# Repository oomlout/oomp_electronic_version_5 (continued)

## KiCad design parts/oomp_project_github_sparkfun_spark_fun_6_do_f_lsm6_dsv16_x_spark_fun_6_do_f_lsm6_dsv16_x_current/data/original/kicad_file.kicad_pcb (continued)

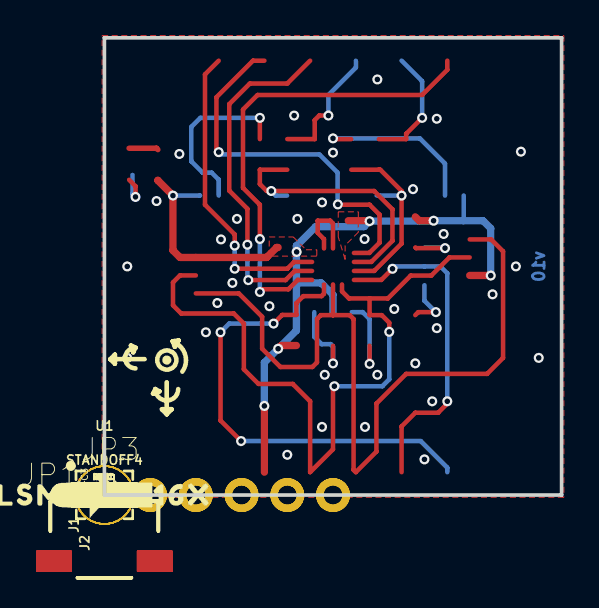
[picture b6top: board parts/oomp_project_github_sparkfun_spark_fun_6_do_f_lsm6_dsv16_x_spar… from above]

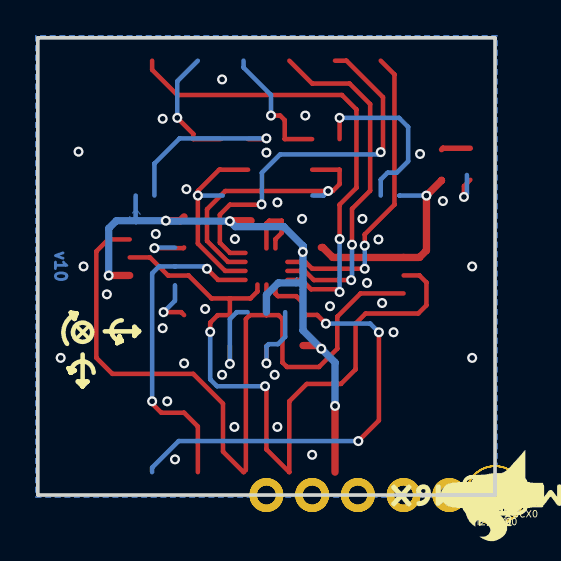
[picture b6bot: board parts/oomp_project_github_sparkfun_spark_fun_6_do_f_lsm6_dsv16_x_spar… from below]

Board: 2 copper layers, 25.4 x 25.4 mm, 87 parts (40 on the bottom side), 22 nets.

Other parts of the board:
U$1, U$15: #3V3#1
U$2, U$17: #GND#0
U$3: ##CS##7
U$4: #SDA#4
U$5: #SCL#5
U$6: #POCI#11
U$7: INT16
U$8: #INT2#2
U$9: OCS17
U$10: SCX18
U$11: SDX19
U$12: #AH1#32
U$13: #0X6A#11
U$14: #0X6B#11
U$16: #LED#4
U$18: #POCI#12
U$19: #AH2#32
U$20: #OCS#32
U$21: #INT1#25
U$23: #PAD1#4
U$24: #POCIX#8
U$25: #I2C#11
U$26: #PICO#13
U$27: ##CS##8
U$28: PWR8
U$29: SFE_LOGO_FLAME_.1
U$30: #PAD2#4
U$31: 6DOF12
U$32: #1#729
U$33: #POCIX#7
U$34, U$37: X2114
U$35, U$38: Y2115
U$36, U$39: Z2116
U$40: #INT2#3
U$41: #1#4
U$42: #SDX#20
U$43: #SCX#19
U$44: SFE_LOGO_FLAME_.2
U$45, U$49: #0#4
U$46, U$47: LSM6DSV16X37
U$48: #SCLK#4

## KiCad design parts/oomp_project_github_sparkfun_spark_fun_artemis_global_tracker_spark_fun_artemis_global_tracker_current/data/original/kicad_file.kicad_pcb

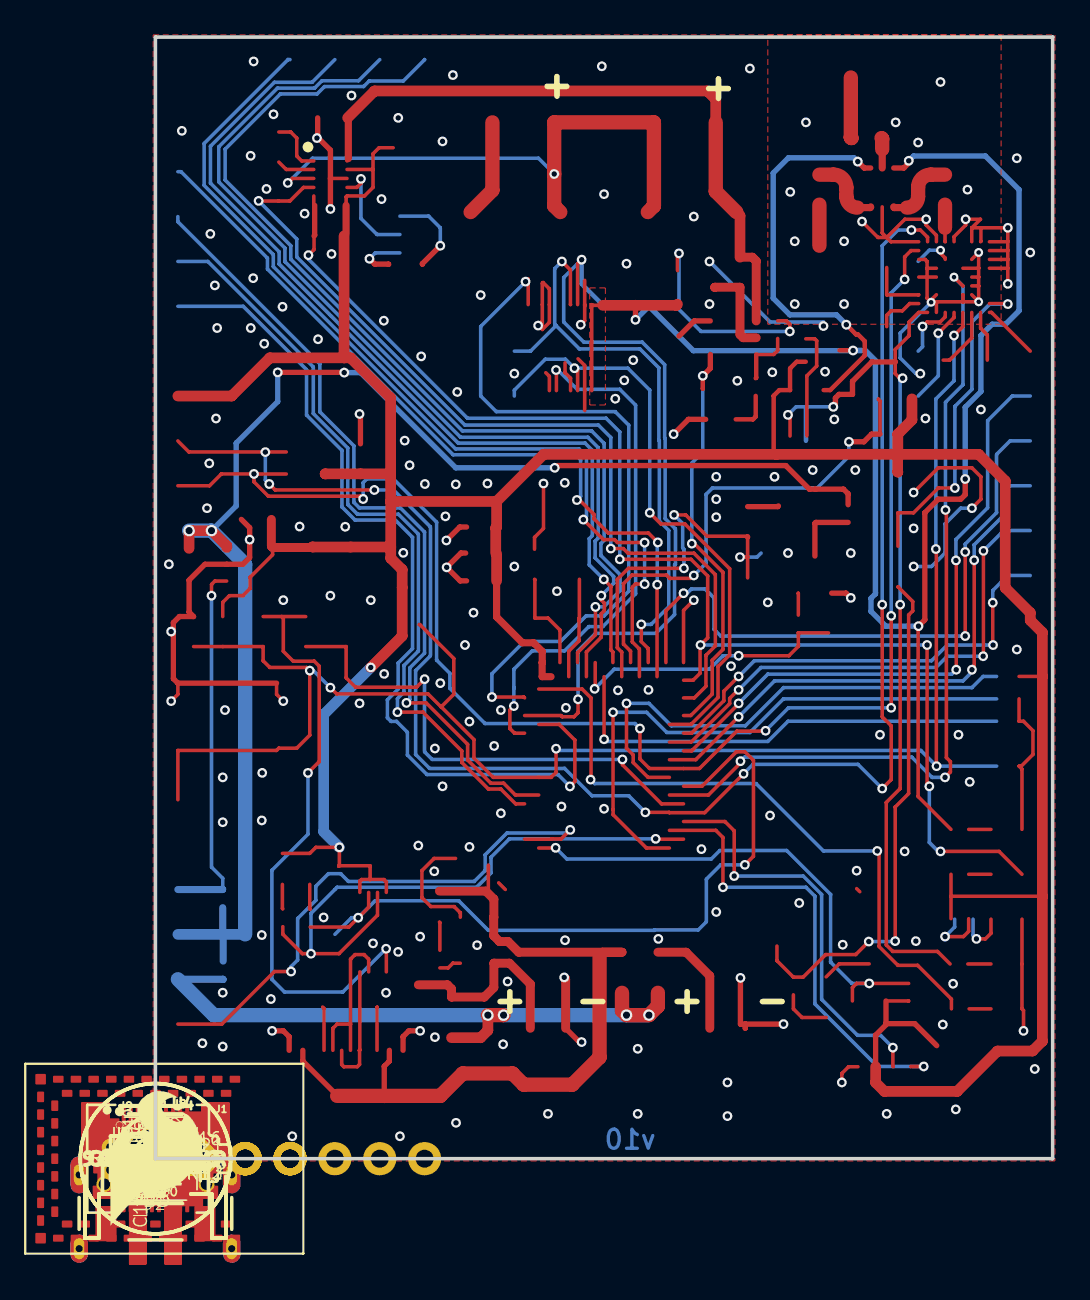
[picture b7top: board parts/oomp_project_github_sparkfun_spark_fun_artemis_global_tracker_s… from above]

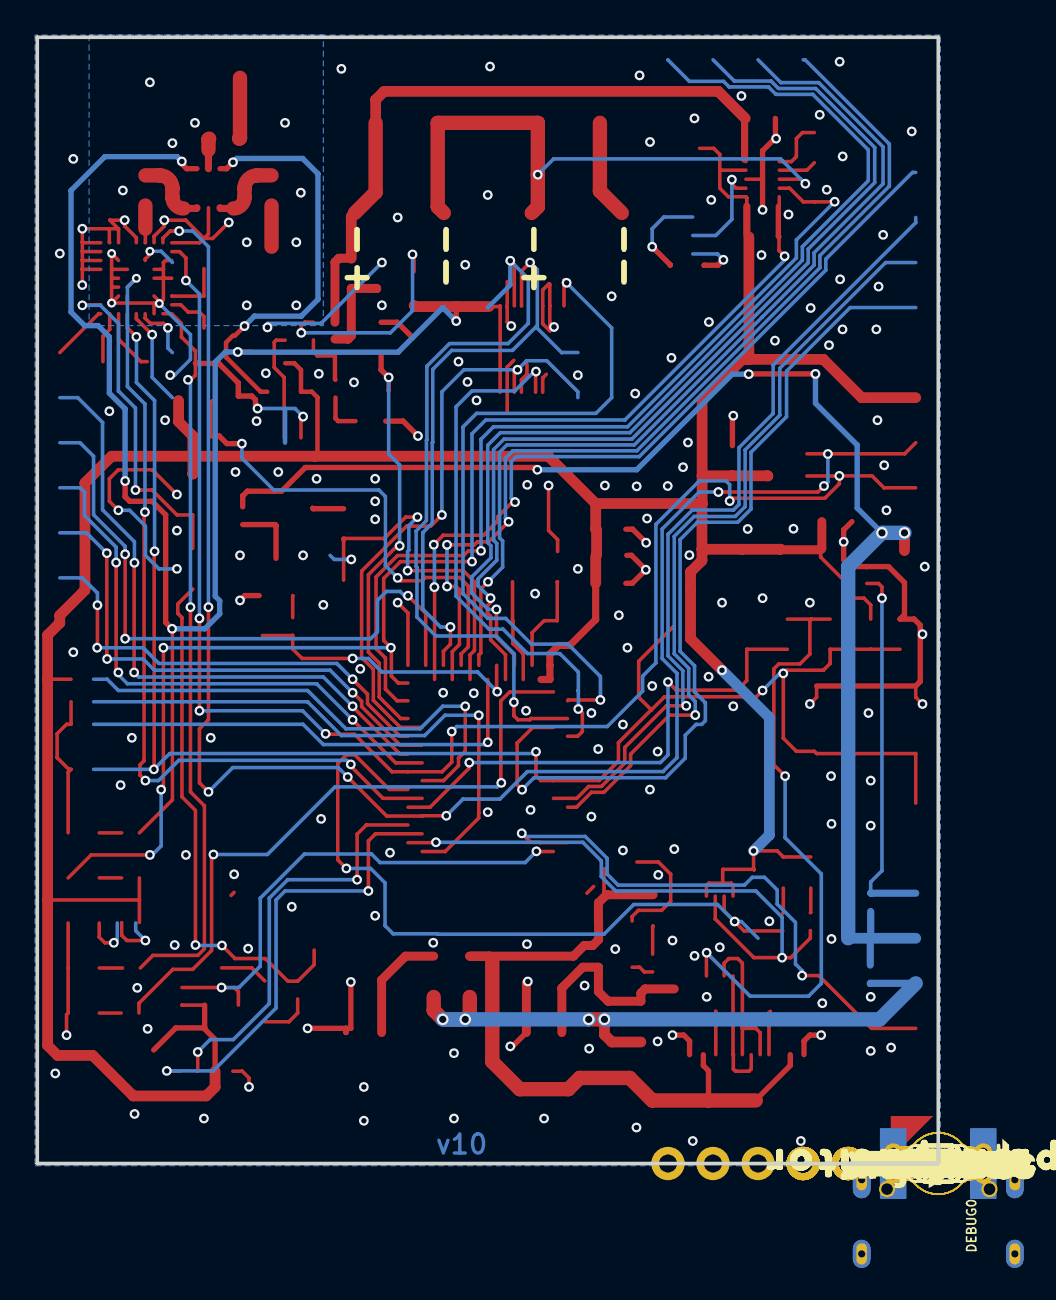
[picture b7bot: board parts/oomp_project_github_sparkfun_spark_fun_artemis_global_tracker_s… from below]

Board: 2 copper layers, 50.8 x 63.5 mm, 240 parts (79 on the bottom side), 101 nets.

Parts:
!RESET0: 1X01_NO_SILK
B1: ML414H_IV01E_BATTERY; ML414H_IV01E
C1, C9: 10nF; 0603
C2: 2.2uF; 0603
C3, C10, C23, C24, C27: 1.0uF; 0603
C4, C12: 0.22uF; 0603
C5, C6: 1F 2.7V; CPOL-RADIAL-1F-2.7V
C7, C13, C20, C28, C30, C31: 0.1uF; 0603
C8, C11, C17: 4.7uF; 0603
C14, C15, C16: 100pF; 0603
C18, C19: 15pF; 0603
C21, C25: 22uF; 0805
C22: 10uF; 0603
C29: 1nF; 0603
D1, D7: GREEN; LED-0603
D2, D9, D13: Yellow; LED-0603
D3: RED; LED-0603
D4: BLUE; LED-0603
D5, D8, D10, D11, D12, D14: 0.5A/40V/420mV; SOD-323
D6: WHITE; LED-0603
D17, D41: PAD.03X.05
DEBUG0: CORTEX_DEBUG; 2X5-PTH-1.27MM-NO_SILK
EN0: 1X01_NO_SILK
FRAME3: FRAME-LETTERNO_PACKAGE; DUMMY
FRAME5: FRAME-LEDGER; CREATIVE_COMMONS
GND0: 1X01_NO_SILK
GPS_RX0: TEST-POINT3X5; PAD.03X.05
GPS_TX0: TEST-POINT3X5; PAD.03X.05
I2C0: PTH; 1X04_NO_SILK
J1: IRIDIUM_9603N
J2: USB-C; USB-C-16P-2LAYER-PADS
J3, J5: JST-2-SMD
J4: 1X02_NO_SILK
J6: U.FL
J7: ANTENNA-GROUNDEDEDGE_SMA; SMA-EDGE
J8, J9: STAND-OFF-REFLOW-M2.0_6.0MM_TALL; STAND-OFF-REFLOW-M2.0
J10, J11: 1X04_NO_SILK
J13: 1X01_NO_SILK
JP1: JUMPER-SMT_3_1-NC_TRACE_SILK; SMT-JUMPER_3_1-NC_TRACE_SILK
JP2: JUMPER-SMT_2_NC_TRACE_SILK; SMT-JUMPER_2_NC_TRACE_SILK
JP7, JP8, JP13, JP14: FIDUCIAL1X2; FIDUCIAL-1X2
JP9, JP10, JP11, JP12: STAND-OFF
L1: 2.2uH; 0806
LOGO1: SFE_LOGO_NAME.1_INCH; SFE_LOGO_NAME_.1
LOGO2: SFE_LOGO_FLAME.3_INCH; SFE_LOGO_FLAME_.3
LOGO4: OSHW-LOGOMINI; OSHW-LOGO-MINI
MEAS0: JUMPER-SMT_2_NC_TRACE_SILK; SMT-JUMPER_2_NC_TRACE_SILK
Q1: 5.8A/30V/35mΩ; SOT23-3
Q2, Q3, Q6: 20V/4.2A/52mΩ/1.4W; SOT23-3
Q4: 600mA/40V; SOT23-3
QWIIC0: QWIIC_RA; JST04_1MM_RA
R1: 330; 0402-TIGHT
R2, R3, R12, R16, R21, R25, R29: 1k; 0402-TIGHT
R4, R20: 5.1k; 0402-TIGHT
R5, R14, R17, R19, R22, R23, R30: 10K; 0402-TIGHT
R6: 12k; 0603
R7: 30.1k; 0603
R8, R26: 100k; 0603
R9: 0.015ohm; 0603
R10, R11: 100; 0402-TIGHT
R13, R28: 2.0K; 0402-TIGHT
R15: 3.3K; 0402-TIGHT
R24: 20k; 0603
R27: 220k; 0603
R31: 20k; 0402-TIGHT
RX0, RX1: TEST-POINT3X5; PAD.03X.05
S1: RESET; TACTILE_SWITCH_SMD_5.2MM
SAFEBOOT0: TEST-POINT3X5; PAD.03X.05
SC1+0, SC1-0, SC2+0, SC2-0: 1X01_NO_SILK
SPI0: 1X07_NO_SILK
TX0, TX1: TEST-POINT3X5; PAD.03X.05
U1: CH340E_MSOP10; MSOP10
U2: LTC3225EDDB; DFN300X200-10L
U3: ADM4210_1TSOT6; TSOT6
U4: u-blox_ZOE_M8Q-0-10; UBLOX_ZOE_M8-0-10
U5: AS179-92LF; SOT65P220X100-6N
U6: MS8607-02BA01
U7: ARTEMIS_MODULESMD; ARTEMIS_FP
U8: V_SUPERVISOR_BD48K24G_2.4V; SOT23-3
U9: MCP73831; SOT23-5
U10: 3.3V; SOT23-5
U11: 74LVC1G04SE; SOT353
U12: 74LVC1G08W5-7; SOT23-5
U$1, U$13: SUPERCAPACITOR151
U$2: #SCK#199608
U$3, U$43: #3V3#0
U$4: #SDA#0
U$5: #USB#C#0
U$6: #SCL#0
U$7: #VIN#158
U$8: #3V3SW#0
U$9: CHARGING9604
U$10: #COPI#9694
U$11: QWIIC_4MM
U$12: LIPO5
U$14, U$15: 10F_2#7V152
U$16: RX06
U$17, U$70: #3V3#153
U$18: TX07
U$19: #AD35#199609
U$20, U$36: #GND#0
U$21: #SDA#153
U$22: #SCL#154
U$24: #AD31#7
U$25: QWIIC_5MM
U$26: #_RST##156
U$27: #EN#157
U$28: #VIN#3#0
U$29: #AD35#0
U$30: ARTEMIS0
U$31: SUPERCAPS6
U$32: #D17#0
U$33: #SAFEBOOT#0
U$34: #TX0#0
U$35: #TX1#0
U$37: #RX#0
U$38: #RX1#0
U$39: #TX#0
U$40: #5#3V#0
U$41: #D41#0
U$42: #RX0#0
U$44: #RESET#162
U$45: #SOLAR#165
U$46: #LIPO#164
U$47: #MEAS#0
U$48: #3V3_#0
U$50: #D4#36
U$51: GLOBAL0
U$52: TRACKER0
U$53: #LIPO#0
U$54: #_EN_#0
U$55: #SOLAR#0
U$56: #USB#C#161
U$57: #3_X_AA#0
U$58: #VBUS#159
U$59: #AD32#152
U$60: #SCK#9696
U$61: #PWR_LED#0
U$63: #D4#5
U$64: #CIPO#2
U$65: #3_X_AAA#0
U$66: #6V_MAX#0
U$67: CHARGE8
U$69: CURRENT9
U$71: #D42#32
U$72: #D37#152
U$73: #D43#43
U$74: #150#61
U$75: #COPI#5
U$76, U$77, U$78: #GND#152
U$79: #A32#44
U$80: #MA#45
U$81: #60#46
U$82: #D43#151
U$83: #D42#151
U$84: #AD31#151
U$85: #AD12#151
U$86: #D15#151
U$87: #AD11#151
U$88: #AD29#151
U$89: #CIPO#151
U$90: #D37#0
U$91: #GND#38
U$92: ##RST##39
U$93: 9603N_PWR40
U$94: POWER9605
U$95: GNSS9606
U$96: D199607
UNK3V3EN0: JUMPER-SMT_2_NC_TRACE_SILK; SMT-JUMPER_2_NC_TRACE_SILK
UNK3V3SW0: PAD.03X.05
UNK5V3: TEST-POINT3X5; PAD.03X.05
VIN/3: TEST-POINT3X5; PAD.03X.05
X1, X2: 32.768kHz; CRYSTAL-SMD-3.2X1.5MM

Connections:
3.3V: C1.1, C2.1, C7.1, C12.1, C20.2, C22.1, C23.1, C24.1, C25.1, C27.1, C28.1, D7.A, D11.A, D13.A, DEBUG0.1, I2C0.2, Q2.2, Q6.2, QWIIC0.2, R1.2, R8.2, R12.2, R17.2, R19.2, R26.2, SPI0.7, U1.7, U1.10, U2.6, U2.9, U6.1, U7.VDD@36, U7.VDD@37, U8.3, U10.5, U11.5, U12.5
3V3SW: C13.1, Q2.3, R16.2, U4.24, U4.25, U12.1, UNK3V3SW0.1
ANTENNA: C16.1, J7.SIG
ARTEMIS_AD11: J11.3, U7.~AD11
ARTEMIS_AD12: J11.1, U7.~AD12
ARTEMIS_AD29: J11.4, U7.~AD29
ARTEMIS_AD31: J10.1, U7.~AD31
ARTEMIS_AD32: J10.4, U7.~AD32
ARTEMIS_BOOT: C30.2, R27.2, U7.BOOT
ARTEMIS_D4: SPI0.6, U7.~D4
ARTEMIS_D5_SCK: SPI0.4, U7.~D5
ARTEMIS_D6_MISO: SPI0.3, U7.~D6
ARTEMIS_D7_MOSI: SPI0.2, U7.D7
ARTEMIS_D8_SCL: I2C0.4, U4.32, U6.8, U7.D8
ARTEMIS_D9_SDA: I2C0.3, U4.2, U6.7, U7.D9
ARTEMIS_D10: U4.50, U7.D10
ARTEMIS_D13: R23.1, R24.2, U7.~AD13, VIN/3.1
ARTEMIS_D15: J11.2, U7.D15
ARTEMIS_D17: D17.1, J1.5, U7.D17
ARTEMIS_D18: J1.19, U7.~D18
ARTEMIS_D19: R21.2, U7.~D19
ARTEMIS_D22: R14.1, U3.3, U7.~D22
ARTEMIS_D24: J1.6, TX1.1, U7.~D24
ARTEMIS_D25: J1.7, RX1.1, U7.~D25
ARTEMIS_D26: Q2.1, R17.1, U7.~D26
ARTEMIS_D27: R5.2, U2.4, U7.~D27
ARTEMIS_D28: D2.C, R8.1, U2.5, U7.~D28
ARTEMIS_D33: DEBUG0.6, U7.~AD33/SWO
ARTEMIS_D34: R25.1, R30.1, U7.AD34
ARTEMIS_D35: SPI0.5, U7.~AD35
ARTEMIS_D37: J13.1, U7.~D37
ARTEMIS_D39_SCL4: QWIIC0.4, U7.~D39
ARTEMIS_D40_SDA4: QWIIC0.3, U7.D40
ARTEMIS_D41: D41.1, J1.12, U7.D41
ARTEMIS_D42: J10.2, U7.~D42
ARTEMIS_D43: J10.3, U7.~D43
ARTEMIS_D44: Q6.1, R19.1, U7.~D44
ARTEMIS_RX0: R2.1, RX0.1, U1.8, U7.RXI-0
ARTEMIS_SWDCK: DEBUG0.4, U7.SWDCK
ARTEMIS_SWDIO: DEBUG0.2, U7.SWDIO
ARTEMIS_TX0: R3.1, TX0.1, U1.9, U7.TXO-0
ARTEMIS_~RESET: !RESET0.1, C29.1, C31.2, DEBUG0.10, R26.1, S1.3, S1.4, U4.20, U7.~RST, U8.2
ARTEMIS_~RTS: C30.1, C31.1, U1.4
CC3: J2.B5, R4.2
CC4: J2.A5, R20.2
D+2: J2.A6, J2.B6, U1.1
D-2: J2.A7, J2.B7, U1.2
EXT_PWR: J1.1, J1.2, Q1.2, R13.2, U5.4, U11.2, UNK5V3.1
GND: B1.-, C1.2, C2.2, C4.2, C6.-, C7.2, C8.2, C9.2, C10.2, C11.2, C12.2, C13.2, C17.2, C18.1, C19.1, C20.1, C21.2, C22.2, C23.2, C24.2, C25.2, C27.2, C28.2, C29.2, D1.C, D3.C, D4.C, D6.C, DEBUG0.3, DEBUG0.5, DEBUG0.9, GND0.1, I2C0.1, J1.3, J1.4, J1.8, J1.13, J1.14, J1.15, J1.18, J2.GND, J2.GND2, J3.1, J5.1, J6.1, J6.2, J7.GND@0, J7.GND@1, J7.GND@2, J7.GND@3, J8.1, J9.1, Q4.2, QWIIC0.1, R4.1, R5.1, R6.1, R7.2, R14.2, R20.1, R23.2, R27.1, R28.1, R30.2, R31.2, S1.1, S1.2, SC2-0.1, SPI0.1, U1.3, U2.8, U2.11, U3.2, U4.1, U4.3, U4.5, U4.7, U4.8, U4.9, U4.10, U4.11, U4.12, U4.17, U4.23, U4.29, U4.31, U4.37, U4.38, U4.39, U4.40, U4.41, U4.44, U4.46, U4.47, U4.49, U5.2, U6.3, U7.GND@1, U7.GND@22, U7.GND@38, U7.GND@39, U7.GND@47, U7.GND@59, U8.1, U9.2, U10.2, U11.3, U12.3
GNSS: C15.2, U4.4
IRIDIUM: C14.2, J6.FEED
LTC3225_VOUT: C4.1, C5.+, R9.2, SC1+0.1, U2.10, U3.6
unnamed: C5.-, C6.+, SC1-0.1, SC2+0.1, U2.3
unnamed: JP1.3, R6.2
unnamed: JP2.2, R1.1
unnamed: JP1.1, R7.1
unnamed: D2.A, R12.1
unnamed: D3.A, R13.1
unnamed: D5.A, Q6.3
unnamed: Q1.3, R9.1, U3.5
unnamed: C3.2, U2.2
unnamed: C3.1, U2.1
unnamed: JP1.2, U2.7
unnamed: Q1.1, R10.1
unnamed: R10.2, R11.1, U3.4
unnamed: C9.1, R11.2
unnamed: C10.1, U3.1
unnamed: L1.2, U4.26
unnamed: C11.1, L1.1, U4.27
unnamed: U4.18, X2.P$2
unnamed: U4.19, X2.P$1
unnamed: D5.C, R15.2
unnamed: D4.A, R16.1
unnamed: D13.C, R2.2
unnamed: D1.A, JP2.1
unnamed: D11.C, D12.C, U4.16
unnamed: SAFEBOOT0.1, U4.34
unnamed: GPS_RX0.1, U4.22
unnamed: GPS_TX0.1, U4.21
unnamed: C14.1, U5.1
unnamed: C15.1, U5.3
unnamed: C16.2, U5.5
unnamed: R31.1, U5.6, U12.4
unnamed: D7.C, R3.2
unnamed: U11.4, U12.2
unnamed: D6.A, R21.1
unnamed: EN0.1, U10.3, UNK3V3EN0.2
unnamed: Q3.1, Q4.3, R22.1
unnamed: R28.2, U9.5
unnamed: D9.C, R29.2
unnamed: R29.1, U9.1
unnamed: Q3.3, R24.1
unnamed: Q4.1, R25.2
VBUS: D8.C, D10.C, D14.C, J4.2, MEAS0.1
VIN: C21.1, J4.1, MEAS0.2, Q3.2, R22.2, U10.1, UNK3V3EN0.1
V_AAA: D10.A, J3.2
V_BATT: C8.1, D8.A, J5.2, U9.3
V_BCKP: B1.+, D12.A, R15.1
V_USB: C17.1, D9.A, D14.A, J2.VBUS1, J2.VBUS2, U9.4
XTALI: C19.2, U7.XI, X1.P$1
XTALO: C18.2, U7.XO, X1.P$2

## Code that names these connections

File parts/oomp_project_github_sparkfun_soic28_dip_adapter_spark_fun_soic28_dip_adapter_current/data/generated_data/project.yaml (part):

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        connected_to:
        - reference: U$3
          pin_number: '2'
          pin_name: RA0/AN0
      - number: '3'
        name: '3'
        electrical_type: passive
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        connected_to:
        - reference: U$3
          pin_number: '3'
          pin_name: RA1/AN1
      - number: '4'
        name: '4'
        electrical_type: passive
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        connected_to:
        - reference: U$3
          pin_number: '4'
          pin_name: RA2/AN2
      - number: '5'
        name: '5'
        electrical_type: passive
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        connected_to:
        - reference: U$3
          pin_number: '5'
          pin_name: RA3/AN3
      - number: '6'
        name: '6'
        electrical_type: passive
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        connected_to:
        - reference: U$3
          pin_number: '6'
          pin_name: RA4/AN4
      - number: '7'
        name: '7'
        electrical_type: passive
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        connected_to:
        - reference: U$3
          pin_number: '7'
          pin_name: RA5/AN4
      - number: '8'
        name: '8'
        electrical_type: passive
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        connected_to:
        - reference: U$3
          pin_number: '11'
          pin_name: RC0
      - number: '12'
        name: '12'
        electrical_type: passive
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        connected_to:
        - reference: U$3
          pin_number: '12'
          pin_name: RC1
      - number: '13'
        name: '13'
        electrical_type: passive
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        connected_to:
        - reference: U$3
          pin_number: '13'
          pin_name: RC2
      - number: '14'
        name: '14'
        electrical_type: passive
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      pin_name: OSC2
    - reference: U$3
      pin_number: '11'
      pin_name: RC0
    - reference: U$3
      pin_number: '12'
      pin_name: RC1
    - reference: U$3
      pin_number: '13'
      pin_name: RC2
    - reference: U$3
      pin_number: '14'
      pin_name: V-USB
    - reference: U$3
      pin_number: '2'
      pin_name: RA0/AN0
    - reference: U$3
      pin_number: '3'
      pin_name: RA1/AN1
    - reference: U$3
      pin_number: '4'
      pin_name: RA2/AN2
    - reference: U$3
      pin_number: '5'
      pin_name: RA3/AN3
    - reference: U$3
      pin_number: '6'
      pin_name: RA4/AN4
    - reference: U$3
      pin_number: '7'
      pin_name: RA5/AN4
    - reference: U$3
      pin_number: '8'
      pin_name: VSS
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        connected_to:
        - reference: U$3
          pin_number: '15'
          pin_name: RC4/D-
      - number: '2'
        name: '2'
        electrical_type: passive
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        connected_to:
        - reference: U$3
          pin_number: '16'
          pin_name: RC5/D+
      - number: '3'
        name: '3'
        electrical_type: passive
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        connected_to:
        - reference: U$3
          pin_number: '17'
          pin_name: TX/RC6
      - number: '4'
        name: '4'
        electrical_type: passive
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        connected_to:
        - reference: U$3
          pin_number: '18'
          pin_name: RX/RC7
      - number: '5'
        name: '5'
        electrical_type: passive
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        connected_to:
        - reference: U$3
          pin_number: '21'
          pin_name: RB0/INT0
      - number: '8'
        name: '8'
        electrical_type: passive
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        connected_to:
        - reference: U$3
          pin_number: '22'
          pin_name: RB1/INT1/AN10
      - number: '9'
        name: '9'
        electrical_type: passive
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        connected_to:
        - reference: U$3
          pin_number: '23'
          pin_name: RB2/INT2/AN8
      - number: '10'
        name: '10'
        electrical_type: passive
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        connected_to:
        - reference: U$3
          pin_number: '24'
          pin_name: RB3/AN9
      - number: '11'
        name: '11'
        electrical_type: passive
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        connected_to:
        - reference: U$3
          pin_number: '25'
          pin_name: RB4/AN11
      - number: '12'
        name: '12'
        electrical_type: passive
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        connected_to:
        - reference: U$3
          pin_number: '26'
          pin_name: RB5/PGM
      - number: '13'
        name: '13'
        electrical_type: passive
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        connected_to:
        - reference: U$3
          pin_number: '27'
          pin_name: RB6/PGC
      - number: '14'
        name: '14'
        electrical_type: passive
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        connected_to:
        - reference: U$3
          pin_number: '28'
          pin_name: RB7/PGD
      size:
        local_graphics:
          measurement: symbol graphics only; excludes pins, properties, and text
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    connected_components:
    - reference: U$3
      pin_number: '15'
      pin_name: RC4/D-
    - reference: U$3
      pin_number: '16'
      pin_name: RC5/D+
    - reference: U$3
      pin_number: '17'
      pin_name: TX/RC6
    - reference: U$3
      pin_number: '18'
      pin_name: RX/RC7
    - reference: U$3
      pin_number: '19'
      pin_name: VSS
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      pin_name: VDD
    - reference: U$3
      pin_number: '21'
      pin_name: RB0/INT0
    - reference: U$3
      pin_number: '22'
      pin_name: RB1/INT1/AN10
    - reference: U$3
      pin_number: '23'
      pin_name: RB2/INT2/AN8
    - reference: U$3
      pin_number: '24'
      pin_name: RB3/AN9
    - reference: U$3
      pin_number: '25'
      pin_name: RB4/AN11
    - reference: U$3
      pin_number: '26'
      pin_name: RB5/PGM
    - reference: U$3
      pin_number: '27'
      pin_name: RB6/PGC
    - reference: U$3
      pin_number: '28'
      pin_name: RB7/PGD
  pcb:
    reference: JP2
    value: M14
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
